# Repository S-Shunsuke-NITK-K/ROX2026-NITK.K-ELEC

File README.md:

# ROX2026の熊本高専（熊本キャンパス）の回路構成

## 概要
広島のmolten [the Box]で行われたROX2026にロボコン部として参加した。

結果としては、九工大RoDEPとの決勝戦の末、13-14で熊本高専（熊本キャンパス）は準優勝という結果になった。

また、ロボットの装飾が評価されクリエイティビティ賞を受賞した。

本githubでは、大会参加時の回路構成について公開する。

大会HP： https://robotics-open-exchange.com/

## 大会に参加したロボット

## 回路構成

## 回路台（ロボット左側面）

## 回路台（ロボット右側面）
後日公開

## 製作した基板
KiCADを使用して設計しています。基板データを確認する際はKiCADを使用してください。  
KiCADダウンロード：https://www.kicad.org/download/

RDK_X5_Board：https://github.com/S-Shunsuke-NITK-K/ROX2026-NITK.K-ELEC/tree/main/RDK_X5_Board  
  
IMU_Board：https://github.com/S-Shunsuke-NITK-K/ROX2026-NITK.K-ELEC/tree/main/IMU_Board  
  
PCU：https://github.com/S-Shunsuke-NITK-K/ROX2026-NITK.K-ELEC/tree/main/PCU  
  
DriveCANHUB：https://github.com/S-Shunsuke-NITK-K/ROX2026-NITK.K-ELEC/tree/main/DriveCANHUB  
  
PowerHUB：https://github.com/S-Shunsuke-NITK-K/ROX2026-NITK.K-ELEC/tree/main/PowerHUB  
  
LPMD：https://github.com/S-Shunsuke-NITK-K/ROX2026-NITK.K-ELEC/tree/main/LPMD  

NeoPixelsControlBoard：https://github.com/S-Shunsuke-NITK-K/ROX2026-NITK.K-ELEC/tree/main/NeoPixelsControlBoard  
  
## その他
電装：https://github.com/S-Shunsuke-NITK-K/ROX2026-NITK.K-ELEC/tree/main/%E9%9B%BB%E8%A3%85

安全対策：https://github.com/S-Shunsuke-NITK-K/ROX2026-NITK.K-ELEC/tree/main/%E5%AE%89%E5%85%A8%E5%AF%BE%E7%AD%96　

基板を安く発注する方法：https://github.com/S-Shunsuke-NITK-K/ROX2026-NITK.K-ELEC/tree/main/%E5%9F%BA%E6%9D%BF%E3%82%92%E5%AE%89%E3%81%8F%E7%99%BA%E6%B3%A8%E3%81%99%E3%82%8B%E6%96%B9%E6%B3%95

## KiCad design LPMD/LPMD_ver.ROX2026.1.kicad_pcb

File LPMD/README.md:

# LPMD

低容量のモータを駆動するためのモータドライバ（LPMD：Low Power Motor Driver）

### コンセプト
・設計は市販基板のパクリ  
　市販の基板：https://www.pololu.com/file/0J503/VNH5019_carrier_schematic.pdf

・製作費は市販基板よりも安くする  
　市販基板：7000円  
　自作基板：2500円  

## 実物

## 回路図

## PCB

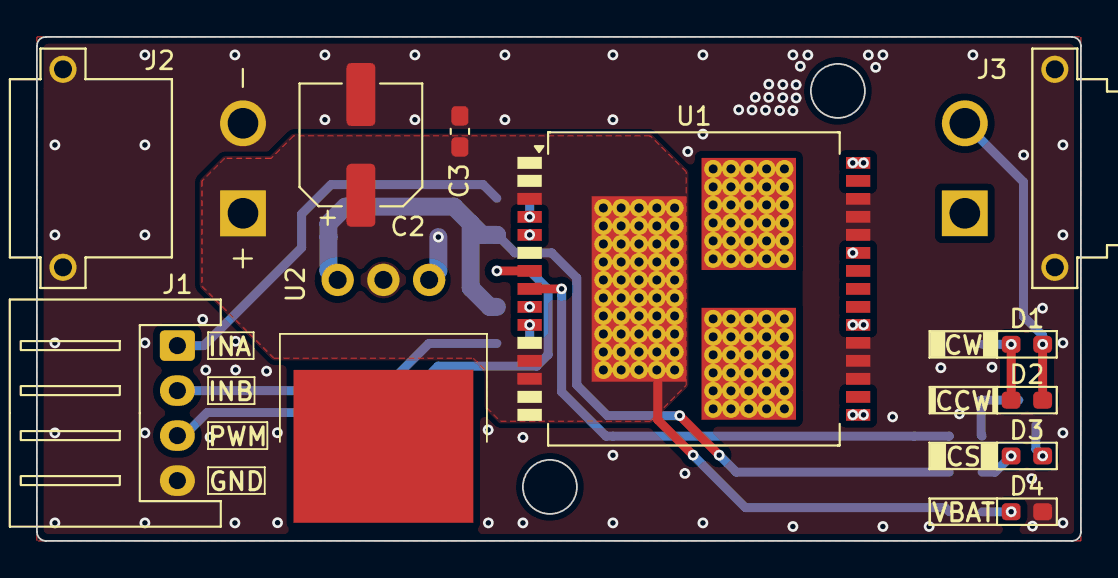
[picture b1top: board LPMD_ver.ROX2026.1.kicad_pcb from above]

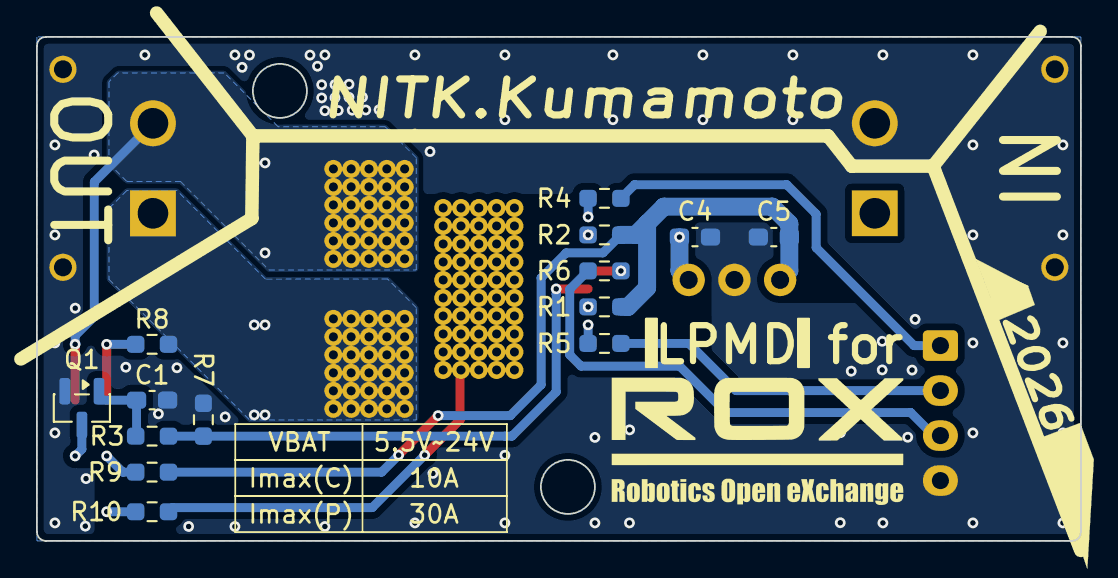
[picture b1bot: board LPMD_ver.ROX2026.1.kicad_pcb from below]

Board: 2 copper layers, 58.0 x 28.0 mm, 25 parts (14 on the bottom side), 19 nets.

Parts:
C1: 33n; C_0603_1608Metric_Pad1.08x0.95mm_HandSolder
C2: 47u; CP_Elec_6.3x5.9
C3: 0.1u; C_0603_1608Metric_Pad1.08x0.95mm_HandSolder
C4, C5: 10u; C_0603_1608Metric_Pad1.08x0.95mm_HandSolder
D1: BLUE; LED_0603_1608Metric_Pad1.05x0.95mm_HandSolder
D2: YELLOW; LED_0603_1608Metric_Pad1.05x0.95mm_HandSolder
D3: RED; LED_0603_1608Metric_Pad1.05x0.95mm_HandSolder
D4: GREEN; LED_0603_1608Metric_Pad1.05x0.95mm_HandSolder
J1: Conn_01x04; JST_XH_S4B-XH-A_1x04_P2.50mm_Horizontal
J2: XT30PW-M; AMASS_XT30PW-M
J3: XT30PW-F; AMASS_XT30PW-F
Q1: MMBT3904; SOT-23
R1, R2: 4.7k; R_0603_1608Metric_Pad0.98x0.95mm_HandSolder
R3, R8, R10: 10k; R_0603_1608Metric_Pad0.98x0.95mm_HandSolder
R4, R5, R6, R7, R9: 1k; R_0603_1608Metric_Pad0.98x0.95mm_HandSolder
U1: VNH5019A-E; ST_MultiPowerSO-30
U2: LM2940T-3.3

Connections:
+3.3V: C5.1, R1.1, R2.1, R9.1, U2.3 (VOUT)
CS: C1.1, Q1.1 (B), R3.1
GND: C1.2, C2.2, C3.2, C4.2, C5.2, D4.1 (K), J1.4, J2.N, J2.S1, J2.S2, J3.S1, J3.S2, Q1.2 (E), R7.2, U1.18 (GNDB), U1.19 (GNDB), U1.20 (GNDB), U1.26 (GNDA), U1.27 (GNDA), U1.28 (GNDA), U2.2 (GND)
INA: J1.1, R4.1
INB: J1.2, R5.1
unnamed: D1.1 (K), D2.2 (A), R8.1
unnamed: D3.2 (A), R9.2
unnamed: D3.1 (K), Q1.3 (C)
unnamed: D4.2 (A), R10.2
unnamed: R3.2, R7.1, U1.8 (CS)
unnamed: R2.2, U1.5 (EN/DIAGA)
unnamed: R1.2, U1.9 (EN/DIAGB)
unnamed: R4.2, U1.4 (INA)
unnamed: R5.2, U1.10 (INB)
unnamed: R6.2, U1.7 (PWM)
OUTA: D1.2 (A), D2.1 (K), J3.N, U1.25 (OUTA), U1.30 (OUTA), U1.33 (OUTA)
OUTB: J3.P, R8.2, U1.16 (OUTB), U1.21 (OUTB), U1.32 (OUTB)
PWM: J1.3, R6.1
VBAT: C2.1, C3.1, C4.1, J2.P, R10.1, U1.3 (VCC), U1.12 (VBAT), U1.13 (VCC), U1.31 (VCC), U2.1 (VIN)

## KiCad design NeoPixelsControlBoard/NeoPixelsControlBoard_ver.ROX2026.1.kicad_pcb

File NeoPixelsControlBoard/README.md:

# NeoPixelsControlBoard
LEDテープを駆動するための電源を生成する基板

### 入力
12V電源（XT60 オス）&LED制御信号（XH2ピン オス）  

### 出力  
5V電源+LED制御信号（XH3ピン オス）  

### コンセプト
・大量のLEDテープを安定動作させるため、DCDCコンバータ（BP5293-50）を用いて12V電源から5V電源を生成する。

・5V電源とLED制御信号を1つのコネクタにまとめたい。

## 3Dモデル

## 回路図

## PCB

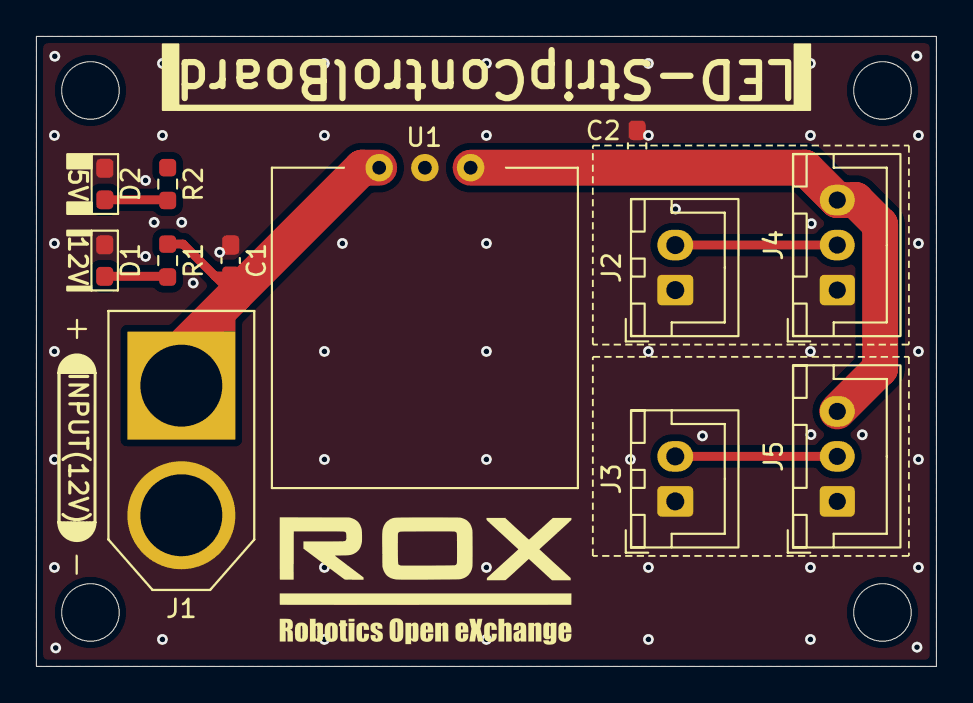
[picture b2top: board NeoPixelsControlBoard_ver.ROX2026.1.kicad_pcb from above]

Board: 2 copper layers, 50.0 x 35.0 mm, 12 parts (0 on the bottom side), 7 nets.

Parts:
C1, C2: 0.1u; C_0603_1608Metric_Pad1.08x0.95mm_HandSolder
D1, D2: RED; LED_0603_1608Metric_Pad1.05x0.95mm_HandSolder
J1: XT60-M; AMASS_XT60-M
J2, J3: Conn_01x02; JST_XH_B2B-XH-A_1x02_P2.50mm_Vertical
J4, J5: Conn_01x03; JST_XH_B3B-XH-A_1x03_P2.50mm_Vertical
R1: 10k; R_0603_1608Metric_Pad0.98x0.95mm_HandSolder
R2: 1k; R_0603_1608Metric_Pad0.98x0.95mm_HandSolder
U1: BP5293-50; BP5293

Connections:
+5V: C2.1, J4.3, J5.3, R2.1, U1.1 (Vi+)
+12V: C1.1, J1.P, R1.1, U1.2 (Vo+)
GND: C1.2, C2.2, D1.1 (K), D2.1 (K), J1.N, J2.1, J3.1, J4.1, J5.1, U1.3 (GND)
NeoPixelsSignal_ch0: J2.2, J4.2
NeoPixelsSignal_ch1: J3.2, J5.2
unnamed: D1.2 (A), R1.2
unnamed: D2.2 (A), R2.2

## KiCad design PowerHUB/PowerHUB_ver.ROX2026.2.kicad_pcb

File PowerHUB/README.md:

# PowerHUB
電源を分配する基板

## 仕様

### 入力
電源（XT60 オス） x1ポート

### 出力  
電源（XT60 メス） x3ポート

### コンセプト
配布されたワンタッチコネクタを使用しても問題はないが、専用コネクタを使用することで「配線の抜き差しが楽になる」「差し間違いの防止」などのメリットが得られる。 

## 3Dモデル

## 回路図

## PCB

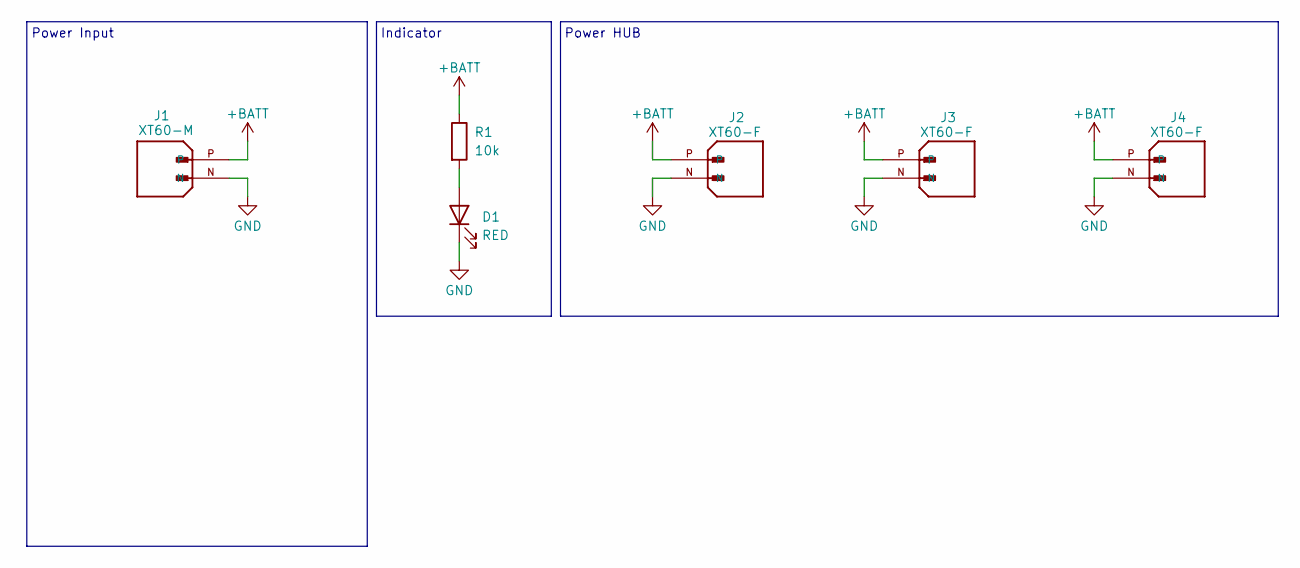
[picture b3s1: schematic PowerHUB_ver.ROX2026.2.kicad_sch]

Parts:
D1: RED; LED_0603_1608Metric_Pad1.05x0.95mm_HandSolder
J1: XT60-M; AMASS_XT60-M; PARTREV V1.2
J2, J3, J4: XT60-F; AMASS_XT60-F; PARTREV V1.2
R1: 10k; R_0603_1608Metric_Pad0.98x0.95mm_HandSolder

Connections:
+BATT: J1.P, J2.P, J3.P, J4.P, R1.1
GND: D1.1 (K), J1.N, J2.N, J3.N, J4.N
unnamed: D1.2 (A), R1.2

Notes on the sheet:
Power Input
Indicator
Power HUB

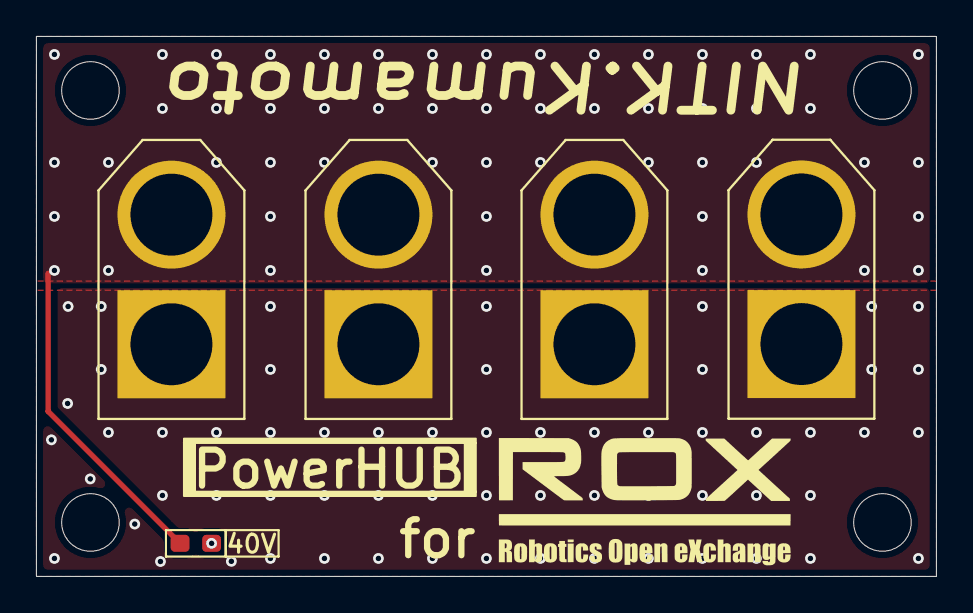
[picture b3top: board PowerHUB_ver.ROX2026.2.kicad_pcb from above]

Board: 2 copper layers, 50.0 x 30.0 mm, 6 parts (1 on the bottom side), 3 nets.

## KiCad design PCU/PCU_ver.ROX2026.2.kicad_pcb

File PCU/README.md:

# PCU
緊急停止スイッチの状態に応じて電源出力をON/OFFする基板（PCU：Power Control Unit）

### 入力
バッテリー電源（XT60 オス）

電源スイッチ（XH2ピン　オス）

緊急停止スイッチ（XH2ピン　オス）

緊急停止信号（XH2ピン　オス）

### 出力  
バッテリー電源（XT60 メス）

### コンセプト
・Fuseを搭載

・電源スイッチと緊急停止スイッチが押されるとリレーの励磁が停止し、電源出力がOFFになる。

・RDK X5から出力される緊急停止信号の状態に応じてリレーの励磁が停止し、電源出力がOFFになる。

・瞬間的な電流不足を補う大容量コンデンサ（10000μf）を搭載&放電回路を搭載

## 3Dモデル

## 回路図

## PCB

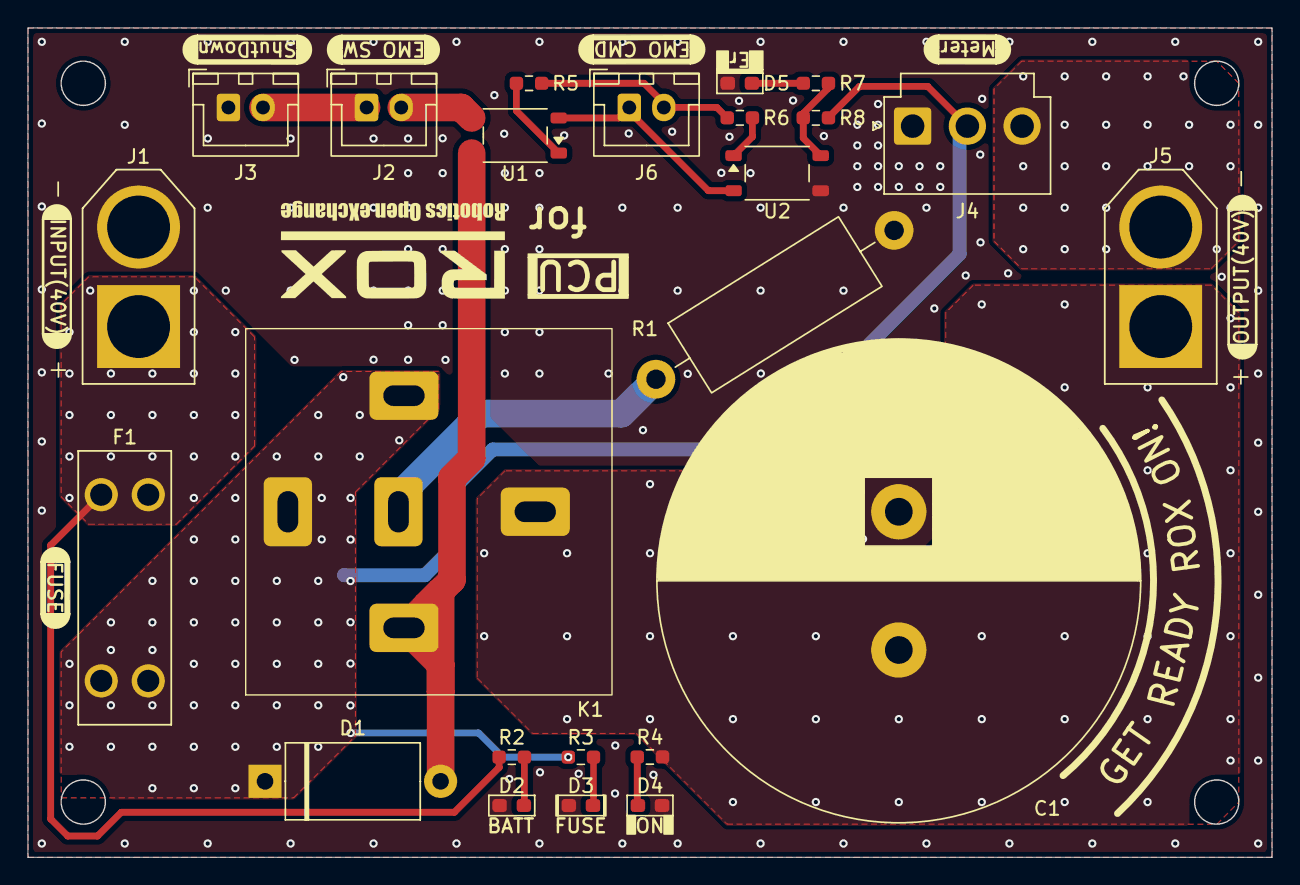
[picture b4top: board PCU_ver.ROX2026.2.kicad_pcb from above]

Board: 2 copper layers, 90.0 x 60.0 mm, 24 parts (0 on the bottom side), 18 nets.

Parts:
C1: 10000u; C_10000
D1: ER504
D2: RED; LED_0603_1608Metric_Pad1.05x0.95mm_HandSolder
D3, D5: ORANGE; LED_0603_1608Metric_Pad1.05x0.95mm_HandSolder
D4: GREEN; LED_0603_1608Metric_Pad1.05x0.95mm_HandSolder
F1: 3557-2; FUSE_3557-2
J1: XT60-M; AMASS_XT60-M
J2: EMO_SW; JST_XH_B2B-XH-A_1x02_P2.50mm_Vertical
J3: ShutDown_SW; JST_XH_B2B-XH-A_1x02_P2.50mm_Vertical
J4: Conn_01x03; JST_VH_B3P-VH-B_1x03_P3.96mm_Vertical
J5: XT60-F; AMASS_XT60-F
J6: EMO_CMD; JST_XH_B2B-XH-A_1x02_P2.50mm_Vertical
K1: A3K1CSP48VDC1.6; A21CSP48VDC1.6
R1: 10/3W; R_Axial_DIN0614_L14.3mm_D5.7mm_P20.32mm_Horizontal
R2, R4: 10k; R_0603_1608Metric_Pad0.98x0.95mm_HandSolder
R3, R7, R8: 15k; R_0603_1608Metric_Pad0.98x0.95mm_HandSolder
R5, R6: 300; R_0603_1608Metric_Pad0.98x0.95mm_HandSolder
U1, U2: TLP175A; Toshiba_SOIC-4-6_4.4x3.6mm_P1.27mm

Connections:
+BATT: F1.1_1, F1.1_2, J1.P, R2.1
+BATTF: D1.1 (K), F1.2_1, F1.2_2, J4.2, K1.1, K1.5, R3.1, R8.1
+BATTO: C1.1, J5.P, K1.3, R4.1
CS: J4.3, J5.N
GND: C1.2, D2.1 (K), D3.1 (K), D4.1 (K), D5.1 (K), J1.N, J3.1, J4.1, R1.2, U2.4
unnamed: D1.2 (A), K1.2, U1.6
unnamed: D2.2 (A), R2.2
unnamed: D3.2 (A), R3.2
unnamed: D4.2 (A), R4.2
unnamed: D5.2 (A), R7.2
unnamed: J2.1, J3.2
unnamed: J2.2, U1.4
unnamed: J6.1, U1.3, U2.3
unnamed: J6.2, R5.1, R6.1
unnamed: K1.4, R1.1
unnamed: R5.2, U1.1
unnamed: R6.2, U2.1
unnamed: R7.1, R8.2, U2.6

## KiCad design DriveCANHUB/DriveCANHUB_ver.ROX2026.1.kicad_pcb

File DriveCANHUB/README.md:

# DriveCANHUB
電源とCAN信号を分配する基板

### 入力
電源（XT60 オス）&CAN信号（XH2ピン オス）  

### 出力  
電源+CAN信号（XT30(2+2) オス）  

### コンセプト
配布されたワンタッチコネクタを使用しても問題はないが、専用コネクタを使用することで「配線の抜き差しが楽になる」「差し間違いの防止」などのメリットが得られる。  

## 3Dモデル

## 回路図

## PCB

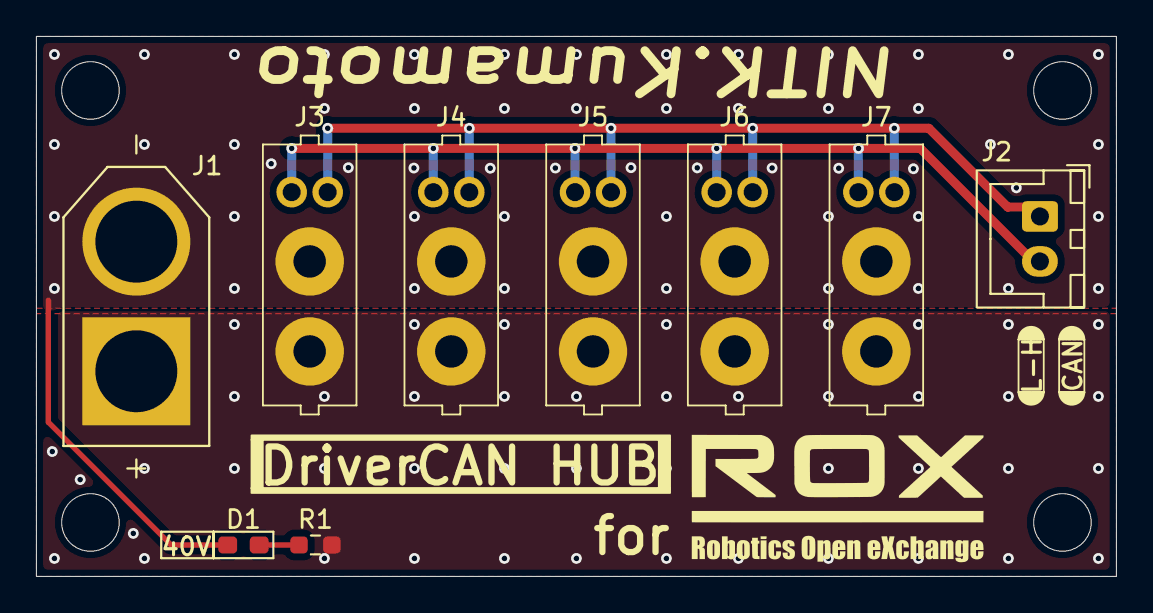
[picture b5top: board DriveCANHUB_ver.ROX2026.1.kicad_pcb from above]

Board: 2 copper layers, 60.0 x 30.0 mm, 9 parts (0 on the bottom side), 5 nets.

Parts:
D1: RED; LED_0603_1608Metric_Pad1.05x0.95mm_HandSolder
J1: XT60-M; AMASS_XT60-M
J2: Conn_01x02; JST_XH_B2B-XH-A_1x02_P2.50mm_Vertical
J3, J4, J5, J6, J7: XT30(2+2)
R1: 10k; R_0603_1608Metric_Pad0.98x0.95mm_HandSolder

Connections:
+BATT: J1.P, J3.P, J4.P, J5.P, J6.P, J7.P, R1.1
CAN_H: J2.1, J3.H (CAN_H), J4.H (CAN_H), J5.H (CAN_H), J6.H (CAN_H), J7.H (CAN_H)
CAN_L: J2.2, J3.L (CAN_L), J4.L (CAN_L), J5.L (CAN_L), J6.L (CAN_L), J7.L (CAN_L)
GND: D1.1 (K), J1.N, J3.N, J4.N, J5.N, J6.N, J7.N
unnamed: D1.2 (A), R1.2

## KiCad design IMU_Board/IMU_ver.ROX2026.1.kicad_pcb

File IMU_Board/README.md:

# IMU_Board

ロボットの姿勢をセンシングするためのIMU（BNO055）をロボットに搭載しやすくするための基板  
使用したIMU：https://akizukidenshi.com/catalog/g/g116996/

### コンセプト
・秋月電子で販売されているIMU基板は取付穴が無く、扱いにくいため、固定しやすいように改善

・可能な限りIMUはロボットの中心に設置したい。

　┗ IMU（BNO055）は加速度センサ、ジャイロ、地磁気センサを融合して姿勢を計算している。  
　　 IMUの設置がロボットの中心から離れれば離れるほど遠心加速度や振動の影響を受けやすくなる。（自説）  
　　 ※IMUをロボットの中心から離れた位置に設置してトラブルが発生したことはない。

## 3Dモデル

## 回路図

## PCB

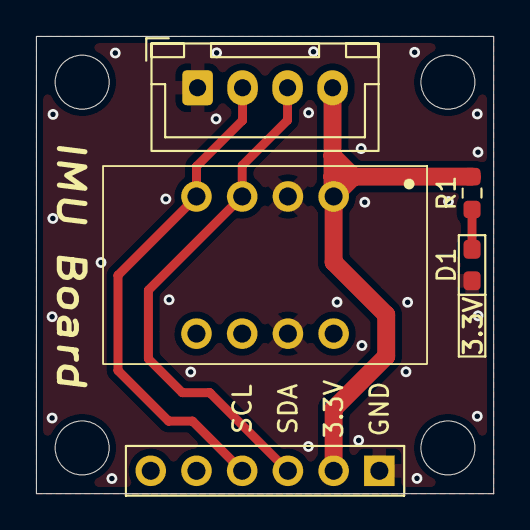
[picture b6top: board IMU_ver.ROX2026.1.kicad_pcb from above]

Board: 2 copper layers, 25.4 x 25.4 mm, 5 parts (0 on the bottom side), 5 nets.

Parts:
D1: RED; LED_0603_1608Metric_Pad1.05x0.95mm_HandSolder
J1: Conn_01x04; JST_XH_B4B-XH-A_1x04_P2.50mm_Vertical
J2: Conn_01x06; PinHeader_1x06_P2.54mm_Vertical
R1: 1k; R_0603_1608Metric_Pad0.98x0.95mm_HandSolder
U1: AE-BNO055-BO

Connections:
+3.3V: J1.4, J2.2, R1.1, U1.1 (VIN)
GND: D1.1 (K), J1.1, J2.1, U1.2 (GND), U1.7 (GND)
unnamed: D1.2 (A), R1.2
SCL: J1.2, J2.4, U1.4 (SCL/R)
SDA: J1.3, J2.3, U1.3 (SDA/T)

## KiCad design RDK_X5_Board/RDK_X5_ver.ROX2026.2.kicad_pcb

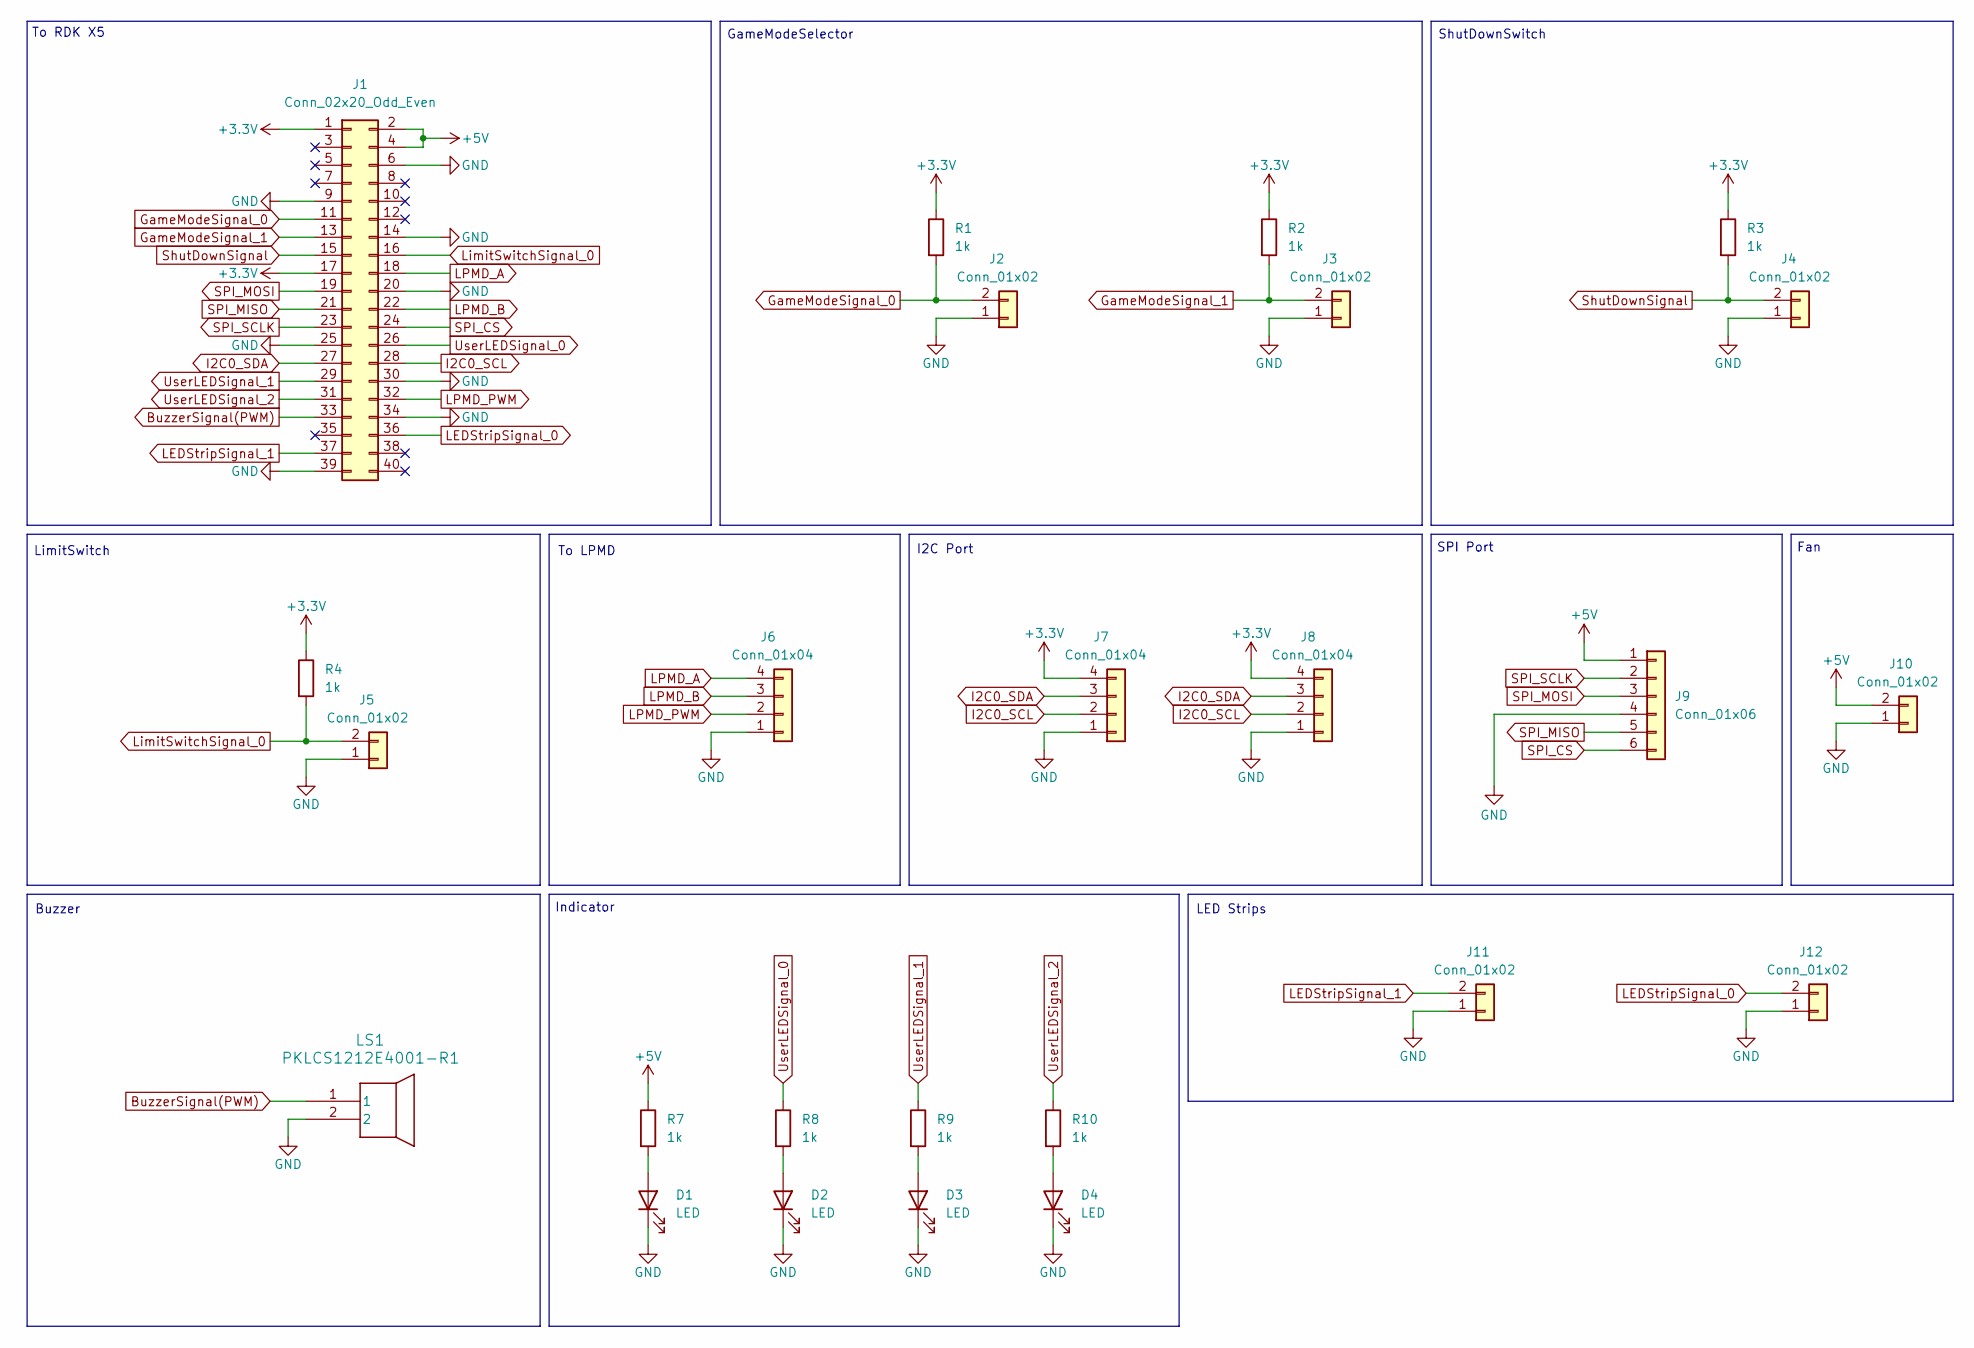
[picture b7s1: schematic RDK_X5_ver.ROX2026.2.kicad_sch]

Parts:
D1, D2, D3, D4: LED; LED_0603_1608Metric_Pad1.05x0.95mm_HandSolder
J1: Conn_02x20_Odd_Even; PinSocket_2x20_P2.54mm_Vertical
J2, J3, J4, J5, J10, J11, J12: Conn_01x02; JST_XH_B2B-XH-A_1x02_P2.50mm_Vertical
J6, J7, J8: Conn_01x04; JST_XH_B4B-XH-A_1x04_P2.50mm_Vertical
J9: Conn_01x06; JST_XH_B6B-XH-A_1x06_P2.50mm_Vertical
LS1: PKLCS1212E4001-R1; PKLCS_472x472_MUR
R1, R2, R3, R4, R7, R8, R9, R10: 1k; R_0603_1608Metric_Pad0.98x0.95mm_HandSolder

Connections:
+3.3V: J1.1, J1.17, J7.4, J8.4, R1.1, R2.1, R3.1, R4.1
+5V: J1.2, J1.4, J9.1, J10.2, R7.1
BuzzerSignal(PWM): J1.33, LS1.1
GND: D1.1 (K), D2.1 (K), D3.1 (K), D4.1 (K), J1.6, J1.9, J1.14, J1.20, J1.25, J1.30, J1.34, J1.39, J2.1, J3.1, J4.1, J5.1, J6.1, J7.1, J8.1, J9.4, J10.1, J11.1, J12.1, LS1.2
GameModeSignal_0: J1.11, J2.2, R1.2
GameModeSignal_1: J1.13, J3.2, R2.2
I2C0_SCL: J1.28, J7.2, J8.2
I2C0_SDA: J1.27, J7.3, J8.3
LEDStripSignal_0: J1.36, J12.2
LEDStripSignal_1: J1.37, J11.2
LPMD_A: J1.18, J6.4
LPMD_B: J1.22, J6.3
LPMD_PWM: J1.32, J6.2
LimitSwitchSignal_0: J1.16, J5.2, R4.2
unnamed: D1.2 (A), R7.2
unnamed: D2.2 (A), R8.2
unnamed: D3.2 (A), R9.2
unnamed: D4.2 (A), R10.2
SPI_CS: J1.24, J9.6
SPI_MISO: J1.21, J9.5
SPI_MOSI: J1.19, J9.3
SPI_SCLK: J1.23, J9.2
ShutDownSignal: J1.15, J4.2, R3.2
UserLEDSignal_0: J1.26, R8.1
UserLEDSignal_1: J1.29, R9.1
UserLEDSignal_2: J1.31, R10.1

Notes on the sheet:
ShutDownSwitch
LED Strips
SPI Port
Indicator
To LPMD
LimitSwitch
Buzzer
To RDK X5
Fan
GameModeSelector
I2C Port

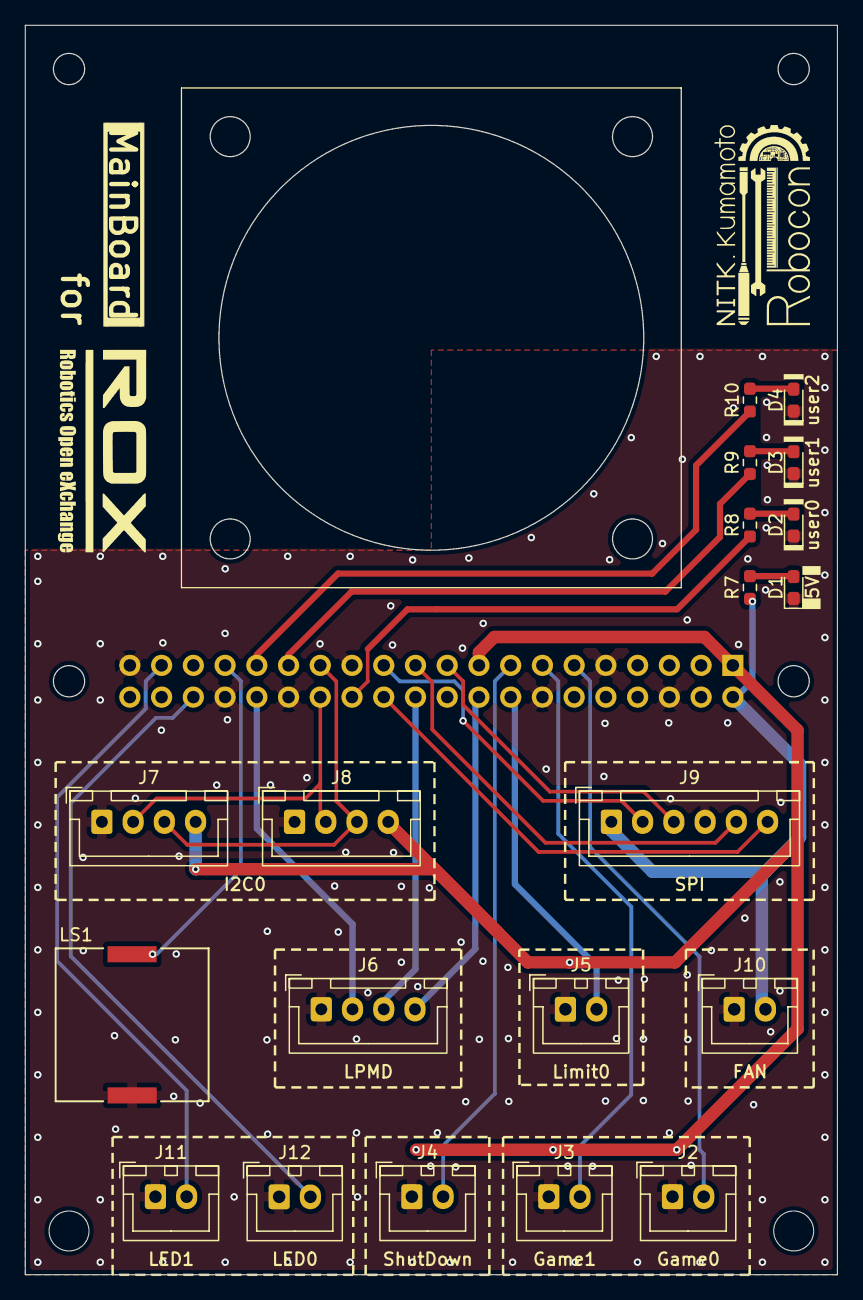
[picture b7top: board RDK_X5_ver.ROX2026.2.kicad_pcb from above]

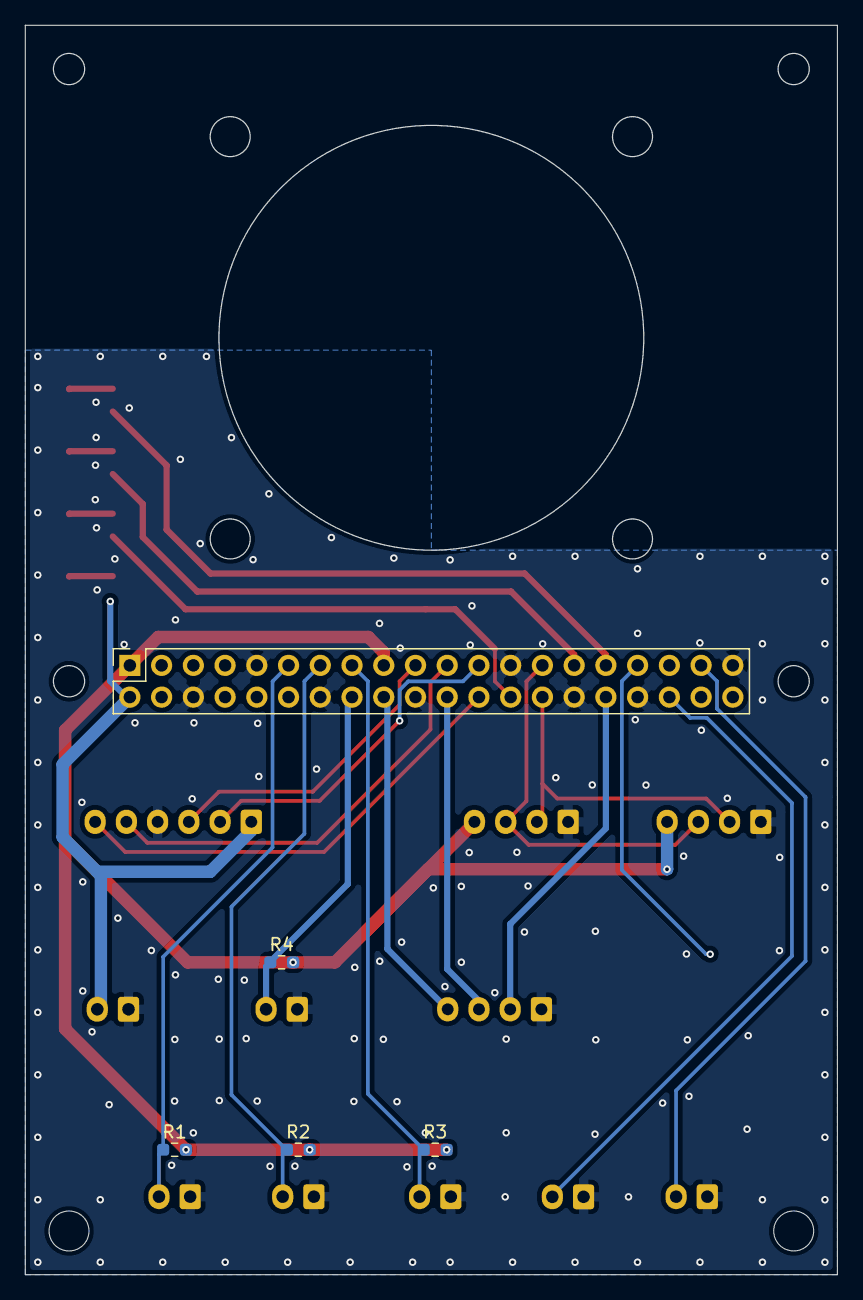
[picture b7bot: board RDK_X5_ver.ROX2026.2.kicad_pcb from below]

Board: 2 copper layers, 65.0 x 100.0 mm, 25 parts (5 on the bottom side), 26 nets.
